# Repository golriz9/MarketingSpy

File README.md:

MarketingSpy
============

ECE411 Practicum Project

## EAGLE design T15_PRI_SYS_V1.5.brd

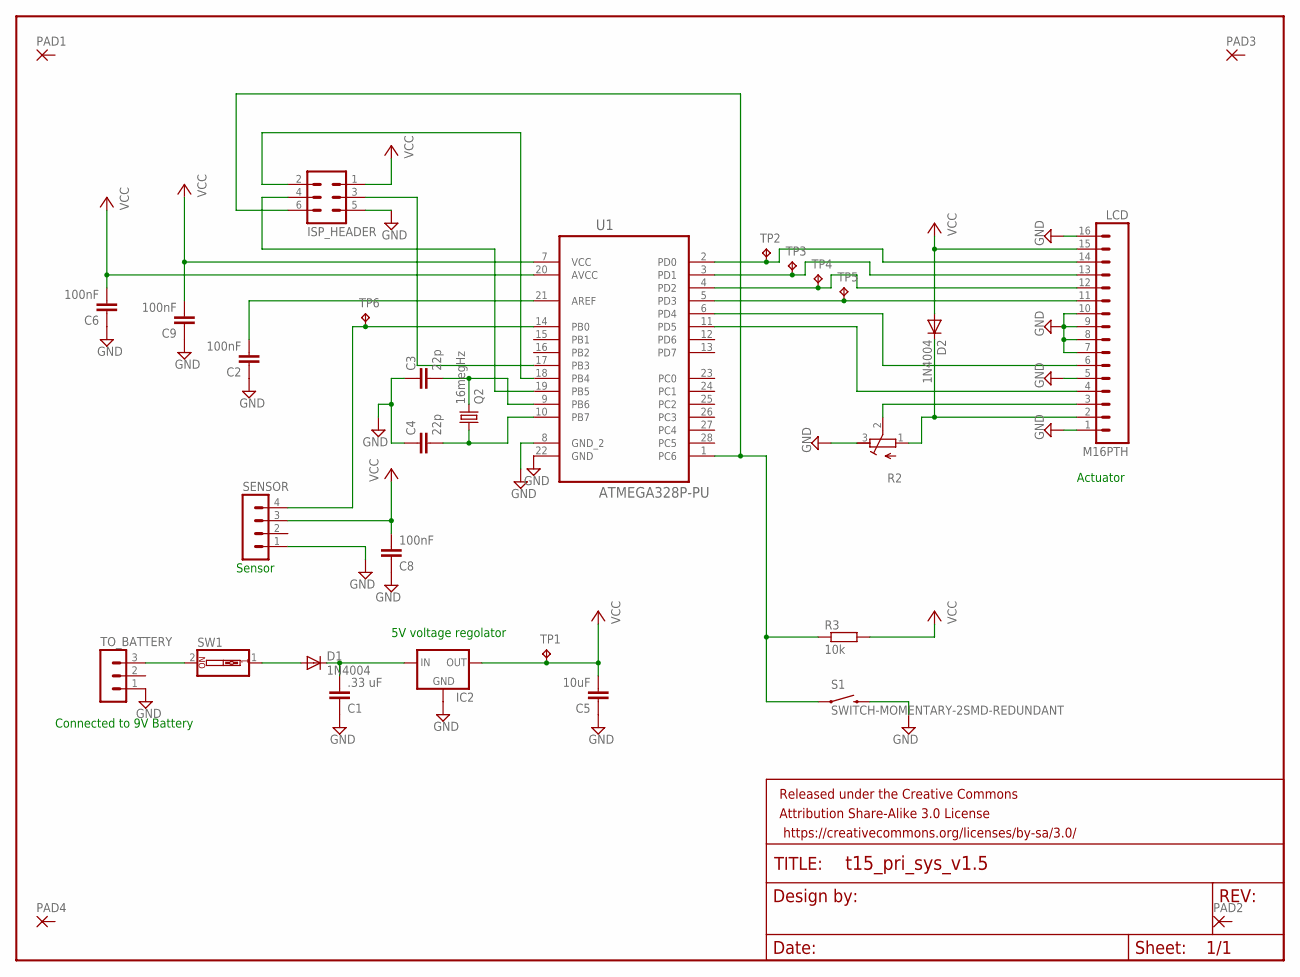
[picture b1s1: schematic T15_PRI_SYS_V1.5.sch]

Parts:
C1: .33 uF; C025-024X044
C2, C6, C8, C9: 100nF; C025-024X044
C3, C4: 22p; C025-024X044
C5: 10uF; C025-024X044
D1, D2: 1N4004; DO41-10
FRAME1: FRAME-LETTER; CREATIVE_COMMONS
IC2: 78XXL
ISP_HEADER: MA03-2
LCD: M16PTH; 1X16
PAD1, PAD2, PAD3, PAD4: 1,6/0,8
Q2: 16megHz; HC49/S
R2: R-TRIMMTS63Z; RTRIMTS63Z
R3: 10k; 0204/5
S1: SWITCH-MOMENTARY-2SMD-REDUNDANT; TACTILE-SWITCH-SMD
SENSOR: MA04-1
SW1: SW_DIP-1; EDG-01
TO_BATTERY: MA03-1
TP1, TP2, TP3, TP4, TP5, TP6: TPB1,27; B1,27
U1: ATMEGA328P-PU; DIP254P762X457-28

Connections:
GND: C1.1, C2.1, C3.1, C4.1, C5.1, C6.1, C8.1, C9.1, IC2.GND, ISP_HEADER.5, LCD.1, LCD.5, LCD.7, LCD.8, LCD.9, LCD.10, LCD.16, R2.3 (E), S1.3 (2), S1.4 (2), SENSOR.1, TO_BATTERY.1, U1.8 (GND_2), U1.22 (GND)
MISO: ISP_HEADER.2, U1.18 (PB4)
MOSI: ISP_HEADER.3, U1.17 (PB3)
unnamed: D2.C, LCD.2, R2.1 (A)
unnamed: LCD.3, R2.2 (S)
unnamed: C1.2, D1.C, IC2.IN
unnamed: C3.2, Q2.2, U1.9 (PB6)
unnamed: LCD.11, TP5.TP, U1.5 (PD3)
unnamed: C4.2, Q2.1, U1.10 (PB7)
unnamed: LCD.12, TP4.TP, U1.4 (PD2)
unnamed: LCD.13, TP3.TP, U1.3 (PD1)
unnamed: LCD.14, TP2.TP, U1.2 (PD0)
unnamed: SW1.2, TO_BATTERY.3
unnamed: LCD.6, U1.6 (PD4)
unnamed: LCD.4, U1.11 (PD5)
unnamed: D1.A, SW1.1
PBO: SENSOR.4, TP6.TP, U1.14 (PB0)
RESET: ISP_HEADER.6, R3.1, S1.1, S1.2 (1), U1.1 (PC6)
SCK: ISP_HEADER.4, U1.19 (PB5)
VCC: C5.2, C6.2, C8.2, C9.2, D2.A, IC2.OUT, ISP_HEADER.1, LCD.15, R3.2, SENSOR.3, TP1.TP, U1.7 (VCC), U1.20 (AVCC)
VCC1: C2.2, U1.21 (AREF)

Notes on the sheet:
Sensor
Actuator
Connected to 9V Battery
5V voltage regolator

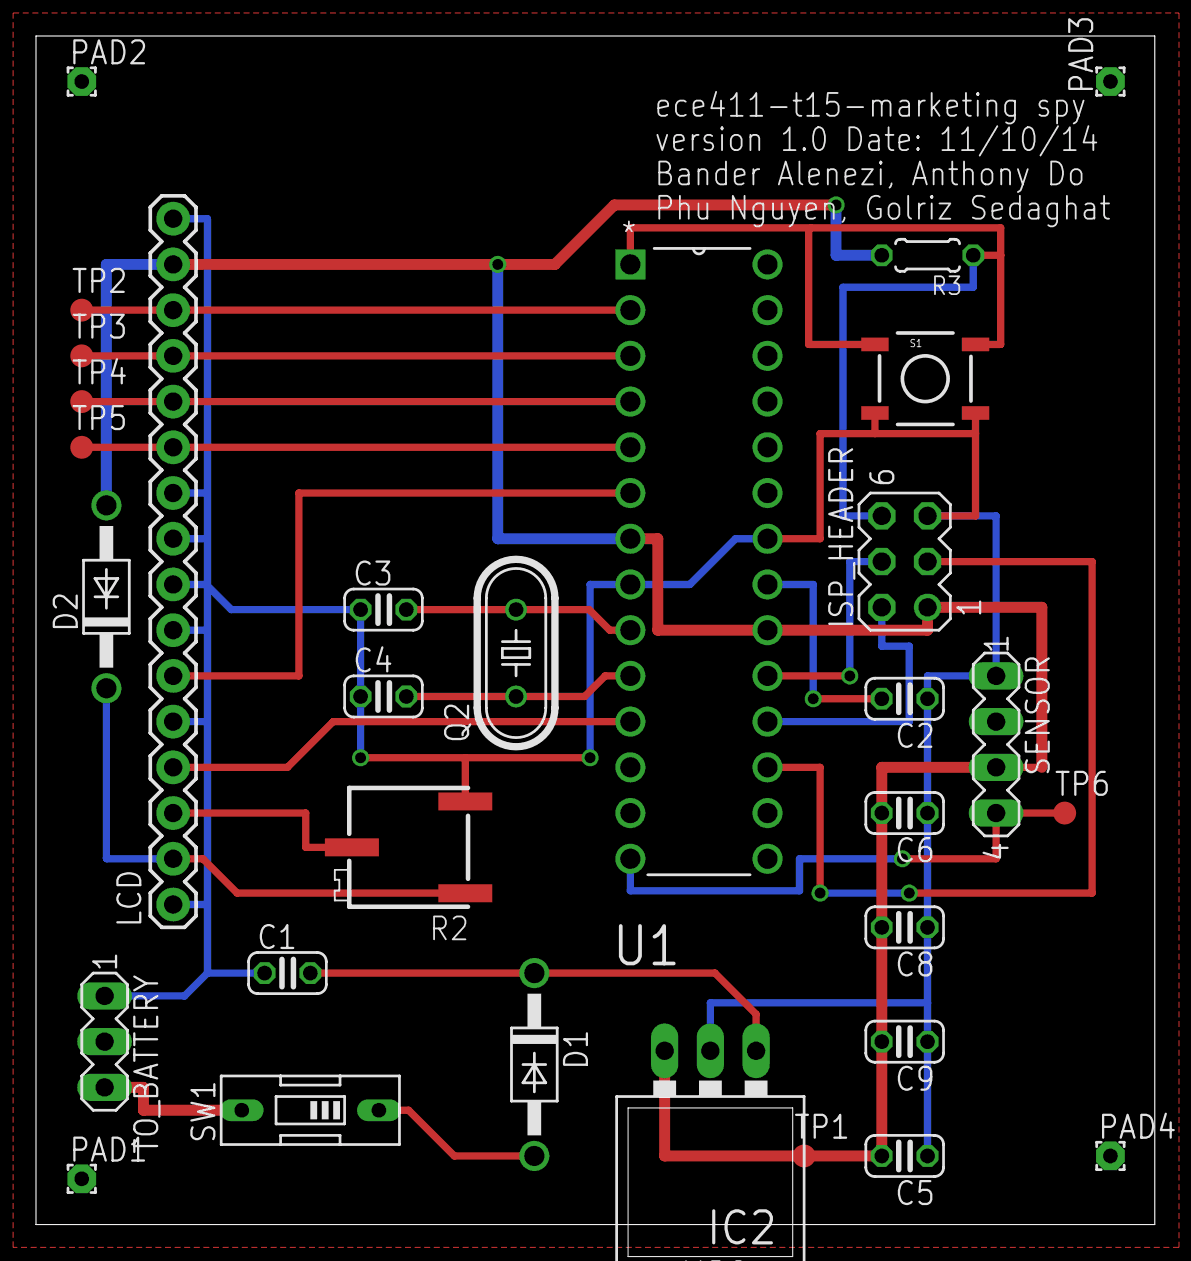
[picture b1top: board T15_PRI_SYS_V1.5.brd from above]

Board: 2 copper layers, 62.2 x 66.0 mm, 32 parts (0 on the bottom side), 21 nets.

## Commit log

2014-11-08 Project description was added
2014-11-08 Decision matrix was added
2014-11-08 Project ideas was added
2014-11-08 Project proposal was added
2014-11-08 Project proposal version one was added
2014-11-08 Project proposal version two was added
2014-11-08 Project requirement document version one was added
2014-11-08 Project block diagram version one was added
2014-11-08 Design analysis version one was added
2014-11-08 Bill of material version one was added
2014-11-08 The guideline of how to set the ID was added
2014-11-08 Document log sheet was added
2014-11-08 Preliminary schematic, version 5, was added
2014-11-08 Project schedule version one was added
2014-11-08 PCB layout version 5 was added
2014-11-08 Schematic version 5 was added
2014-11-08 Create Project Proposal
2014-11-08 Files were added to the wiki
2015-01-15 Create Testing
2015-01-15 Create NP1
2015-01-15 Create test1
2015-01-16 first try
2015-01-16 MatLab subplot example
2015-01-16 Revert "Delete myfile.txt"
    This reverts commit f2062f95183a27798e85a0fe07a179b4ca91313b.
2015-01-16 Revert "Delete test1"

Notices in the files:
parts and their libraries:
SparkFun-Retired: Licensing:Creative Commons ShareAlike 4.0 International - https://creativecommons.org/licenses/by-sa/4.0
SparkFun-Retired: Released under the Creative Commons Attribution Share-Alike 3.0 License
SparkFun-Retired: https://creativecommons.org/licenses/by-sa/3.0
